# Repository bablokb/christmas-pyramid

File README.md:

A 3D-printed, Motor-driven Christmas Pyramid
============================================

Introduction
------------

This project is about building a christmas pyramid with a motor driven
turntable, lightning and music (click on the image above to see it in
action). There are three distinct parts: the electronics, the software
and the 3D-design. A fourth part, a selfmade pcb is also available,
but not necessary. I only use it because it minimizes cables.

The electronics uses cheap parts that are widely available. The software is
implemented in CircuitPython and mostly portable. The 3D build uses
easy to print parts that can be assembled without glue.

Besides the "big" version with multiple levels, a simplified version is
also available:

This version only has three printed parts: the base, the wall and the
plate. It uses a neopixel-ring instead of LEDs, otherwise
it uses the same electronics as the normal version of the pyramid.

Details
-------

Read about

  - [Electronics](./doc/electronics.md)
  - [Software](./doc/software.md)
  - [3D-Printing](./doc/printing.md)
  - [Support-PCB](./doc/pcb.md)

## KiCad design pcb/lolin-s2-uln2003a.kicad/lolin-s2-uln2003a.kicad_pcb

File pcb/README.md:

KiCAD Source Files for the Support PCB
======================================

For details, read [pcb.md](../doc/pcb.md).

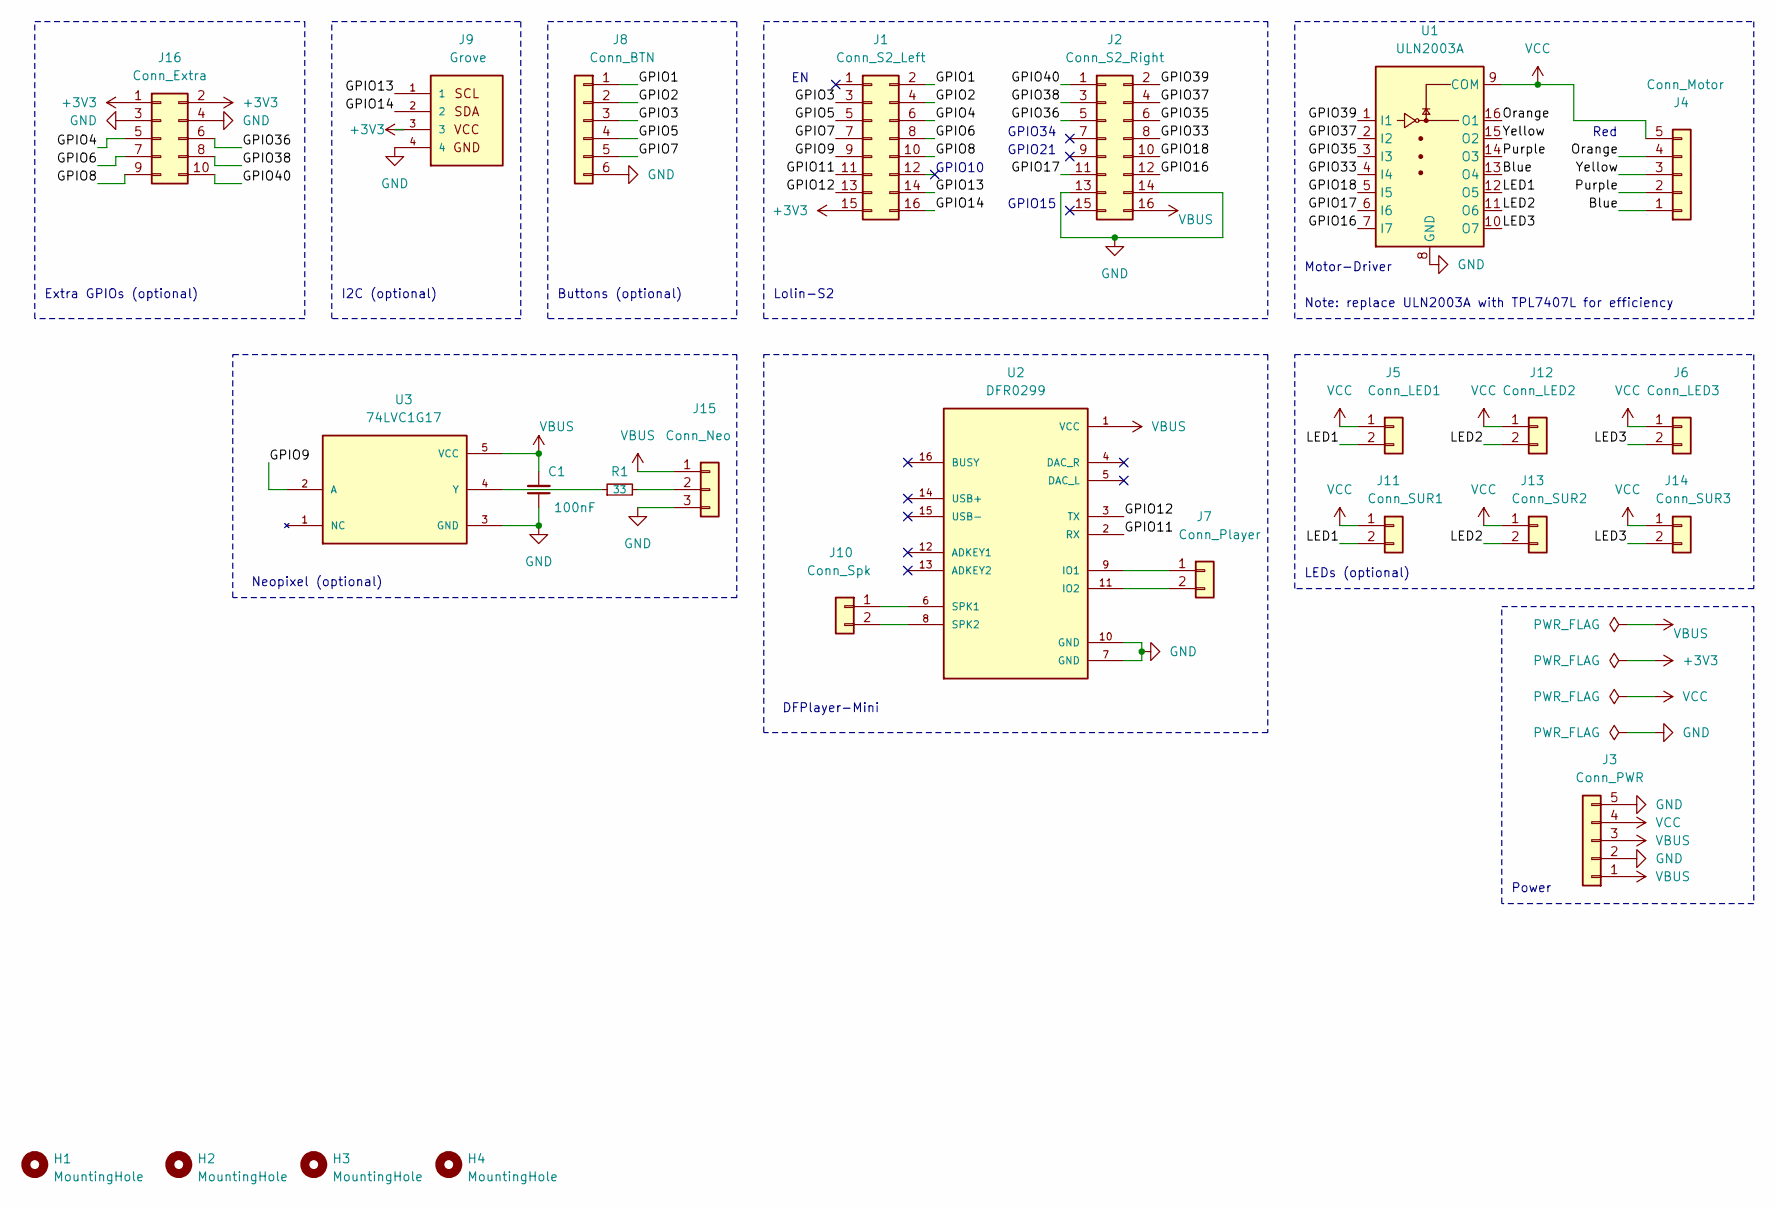
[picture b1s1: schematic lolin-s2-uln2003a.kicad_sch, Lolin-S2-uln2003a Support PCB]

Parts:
C1: 100nF; C_0402_1005Metric; LCSC C1525
H1, H2, H3, H4: MountingHole; MountingHole_2.5mm
J1: Conn_S2_Left; PinSocket_2x08_P2.54mm_Vertical
J2: Conn_S2_Right; PinSocket_2x08_P2.54mm_Vertical
J3: Conn_PWR; PinHeader_1x05_P2.54mm_Vertical
J4: Conn_Motor; JST_XH_B5B-XH-A_1x05_P2.50mm_Vertical
J5: Conn_LED1; JST_XH_B2B-XH-A_1x02_P2.50mm_Vertical
J6: Conn_LED3; JST_XH_B2B-XH-A_1x02_P2.50mm_Vertical
J7: Conn_Player; JST_XH_B2B-XH-A_1x02_P2.50mm_Vertical
J8: Conn_BTN; PinHeader_1x06_P2.54mm_Vertical
J9: Grove; grove_horizontal
J10: Conn_Spk; JST_XH_B2B-XH-A_1x02_P2.50mm_Vertical
J11: Conn_SUR1; JST_SUR_BM02B-SURS-TF_1x02-1MP_P0.80mm_Vertical; LCSC C385130
J12: Conn_LED2; JST_XH_B2B-XH-A_1x02_P2.50mm_Vertical
J13: Conn_SUR2; JST_SUR_BM02B-SURS-TF_1x02-1MP_P0.80mm_Vertical; LCSC C385130
J14: Conn_SUR3; JST_SUR_BM02B-SURS-TF_1x02-1MP_P0.80mm_Vertical; LCSC C385130
J15: Conn_Neo; JST_XH_B3B-XH-A_1x03_P2.50mm_Vertical
J16: Conn_Extra; PinHeader_2x05_P2.54mm_Vertical
R1: 33; R_0402_1005Metric; LCSC C25105
U1: ULN2003A; SOP-16_3.9x9.9mm_P1.27mm; LCSC C7512
U2: DFR0299
U3: 74LVC1G17; 74LVC1G17GW_125; LCSC C426705

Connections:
+3V3: J1.15, J9.3, J16.1, J16.2
/Blue: J4.1, U1.13 (O4)
/GPIO1: J1.2, J8.1
/GPIO2: J1.4, J8.2
/GPIO3: J1.3, J8.3
/GPIO4: J1.6, J16.5
/GPIO5: J1.5, J8.4
/GPIO6: J1.8, J16.7
/GPIO7: J1.7, J8.5
/GPIO8: J1.10, J16.9
/GPIO9: J1.9, U3.2 (A)
/GPIO11: J1.11, U2.2 (RX)
/GPIO12: J1.13, U2.3 (TX)
/GPIO13: J1.14, J9.1
/GPIO14: J1.16, J9.2
/GPIO16: J2.12, U1.7 (I7)
/GPIO17: J2.11, U1.6 (I6)
/GPIO18: J2.10, U1.5 (I5)
/GPIO33: J2.8, U1.4 (I4)
/GPIO35: J2.6, U1.3 (I3)
/GPIO36: J2.5, J16.6
/GPIO37: J2.4, U1.2 (I2)
/GPIO38: J2.3, J16.8
/GPIO39: J2.2, U1.1 (I1)
/GPIO40: J2.1, J16.10
/LED1: J5.2, J11.2, U1.12 (O5)
/LED2: J12.2, J13.2, U1.11 (O6)
/LED3: J6.2, J14.2, U1.10 (O7)
/Orange: J4.4, U1.16 (O1)
/Purple: J4.2, U1.14 (O3)
/Yellow: J4.3, U1.15 (O2)
GND: C1.1, J2.13, J2.14, J3.2, J3.5, J8.6, J9.4, J15.3, J16.3, J16.4, U1.8 (GND), U2.7 (GND), U2.10 (GND), U3.3 (GND)
unnamed: J7.1, U2.9 (IO1)
unnamed: J7.2, U2.11 (IO2)
unnamed: J10.1, U2.6 (SPK1)
unnamed: J10.2, U2.8 (SPK2)
unnamed: J15.2, R1.2
unnamed: R1.1, U3.4 (Y)
VBUS: C1.2, J2.16, J3.1, J3.3, J15.1, U2.1 (VCC), U3.5 (VCC)
VCC: J3.4, J4.5, J5.1, J6.1, J11.1, J12.1, J13.1, J14.1, U1.9 (COM)

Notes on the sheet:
Lolin-S2
Buttons (optional)
Note: replace ULN2003A with TPL7407L for efficiency
Motor-Driver
Neopixel (optional)
GPIO21
GPIO34
GPIO10
Red
Power
Extra GPIOs (optional)
GPIO15
DFPlayer-Mini
LEDs (optional)
I2C (optional)

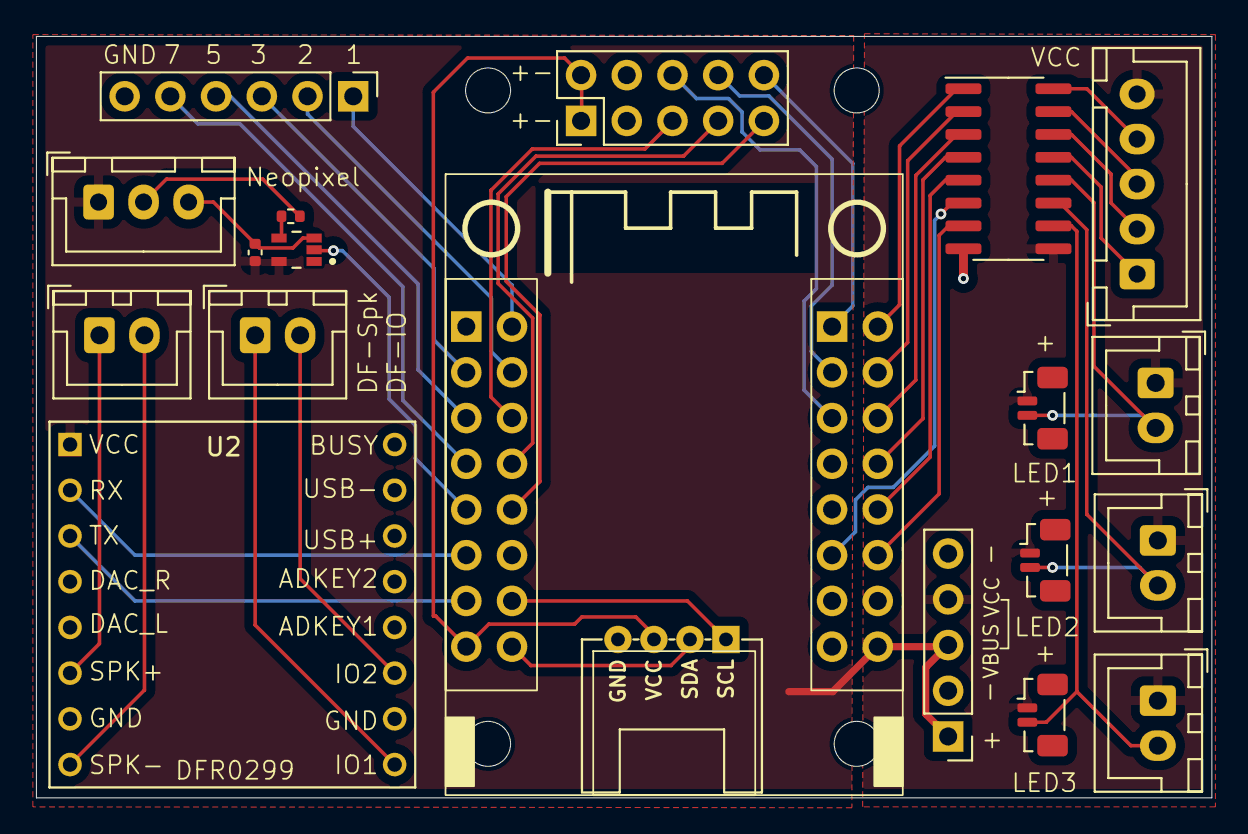
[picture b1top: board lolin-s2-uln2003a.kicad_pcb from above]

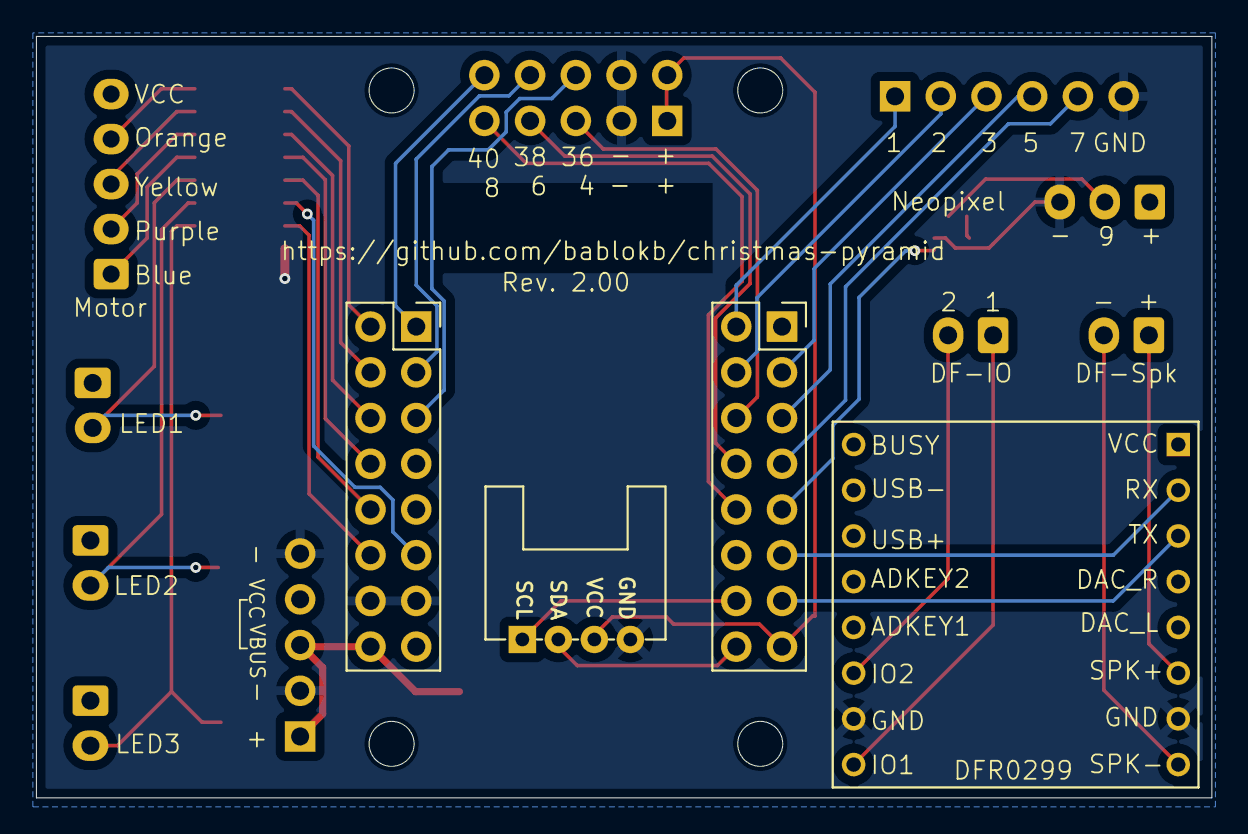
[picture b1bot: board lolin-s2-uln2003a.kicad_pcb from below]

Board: 2 copper layers, 65.3 x 42.3 mm, 25 parts (2 on the bottom side), 40 nets.

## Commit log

2025-06-16 Rev. 1.00 files for motor-pcb
2025-06-16 created .gitignore
2025-06-16 added wip notice
2025-06-17 first draft base of pyramid
2025-06-17 change inner diameter of motor-support
2025-06-17 set base-size to 85
2025-06-17 fix position of pcb-holder
2025-06-20 initial version pcb-holder
2025-06-20 add cutout for SD-card
2025-06-20 use parameters for wall-cutout
2025-06-20 add wall-cutout, fix pcb-holder orientation
2025-06-20 post(): use cyl for preview and star for final rendering
2025-06-20 fine-tune cutouts, cone and total height
2025-06-24 added cutout for LED-cable from base to first level
2025-06-27 add models for base-level walls
2025-06-27 model for LED-strips (for background lighting)
2025-06-28 wall_pcb(): add cutouts for air-flow
2025-06-28 add cutout for air-flow
2025-06-28 tilt cutout for LED-cable
2025-07-02 enlarge USB-C cutout
2025-07-07 add cutout for motor-cable
2025-07-07 fix: post(): add cone alignment to BOTTOM+CENTER
2025-07-07 add 'level_scale'
2025-07-07 initial design level1
2025-07-10 add cutouts to outer posts and cutouts to floor
2025-07-10 add dimensions for level1
2025-07-10 first iteration fences for level1
2025-07-11 fence-posts: only cutout upper third to increase stability
2025-07-11 add cutout height for fence-posts
2025-07-11 add cutouts for fences because cutout of posts are no longer full height
2025-07-14 implement button-holder
2025-07-14 add button-holder to wall_pcb()
2025-07-14 fine tune inner cutout fence-post
2025-07-16 fine-tune cutout for USB-C
2025-07-16 add some more cutout-depth for fences (simplify 3D-printing)
2025-07-16 added cable-holders
2025-07-18 fence-post: fine-tune cutout for base-cone
2025-07-18 add chamfer
2025-07-19 reordered base-plate objects; added module lamp_shade()
2025-07-19 fine tune fence-post cutout again
2025-07-21 initial commit of source-code
2025-07-21 exclude 'lib'
2025-07-21 refactored turntable-plate to tt_plate.scad
2025-07-21 change from 6 to 4 level1-posts
2025-07-21 refactor dimensions from tt_plate.scad to shared.scad
2025-07-21 wait at most config.WAIT4CONSOLE seconds for console
2025-07-22 move level1-posts to the center
2025-07-22 cutouts for level1-posts only in the upper third
2025-07-22 removed some trailing white-space
2025-07-22 use different effect
2025-07-22 fix next/prev file-switching
2025-07-23 added nativity-fence; fine-tune all fences
2025-07-24 add dimensions for level1 walls
2025-07-24 replace hard-coded values with values from shared.scad
2025-07-24 designed walls for level1
2025-07-30 add level2 dimensions
2025-07-30 initial implementation of level2
2025-08-02 callbacks: add debug-messages
2025-08-02 fix: expose inc_rpm() instead of set_rpm()
2025-08-02 fix: don't switch to next song when current song was interrupted
2025-08-08 reduce level2 fence height
2025-08-08 add cutout for cable
2025-08-14 add cutouts for all posts
2025-08-14 add cutouts for central plate, hole and cable
2025-08-14 add a central plate
2025-08-19 added PINS_SD
2025-08-25 switch to different gear-ratio; turn debugging off
2025-08-25 fixed gain-labels on F.Silkscreen
2025-08-25 fixed rotation of motor-connector
2025-08-25 symmetric mounting holes
2025-08-25 update after fixing unsymmetric mounting holes
2025-08-25 remove label J9
2025-08-25 update images
2025-08-25 update due to production-file generation
2025-08-25 updated gerber-files for Revision 1.01
2025-08-27 add pins for DFPlayer (UART)
2025-08-27 switch to new player implementation
2025-08-27 minor change in message-text
2025-08-27 switch implementation from I2S to DFPlayer
2025-08-29 Rev. 2.00 of support-pcb
2025-09-09 pcb_holder: updated screw-offsets for Rev 2.00 board
2025-09-09 larger offset for cable-holders
2025-09-11 simplify lamp_shade()
2025-09-11 adapt for Rev 2.00 PCB
2025-09-15 add src/lib to repository
2025-09-15 provide library-files as part of the repo
2025-09-17 flip orientation of button-holder
2025-09-17 improve pcb-wall
2025-09-17 added documentation
2025-09-17 added model-files for silhouettes/cutouts
2025-09-17 added note about production-files
2025-09-18 pcb_holder(): refactor special supports to pcb_holder_special() (and use this in base.scad)
2025-09-20 be more specific about necessary mcu-pins
2025-09-20 initial content
2025-09-20 added/fixed links to images
2025-09-20 added images
2025-09-20 fixed spelling of filename
2025-09-20 fix markup
2025-09-22 support subset of buttons/callbacks
2025-09-22 activate second and third channel
2025-09-22 also pass callback-numbers to Buttons-constructor
2025-09-22 fix: pause(): toggle self._playing
2025-09-22 added image of Lego-Lighting wires
2025-09-25 run(): add explicit play() after random()
2025-09-25 design change: higher, with cutouts for spots
2025-09-26 fixed size of cutouts for spots
2025-09-26 refactoring: move code for cable-channels to module c_channels()
2025-09-26 redesign: move cable-channels to level2
2025-09-26 increased size of level2-posts/level2-fence
2025-09-26 fix: layer-height for level2-fence/figures
2025-09-27 initial version simple base
2025-09-27 added USB-C cutout
2025-09-27 refactored motor-dimensions to motor_dims.scad
2025-09-27 doubled height of motor-posts
2025-09-27 code cleanup (dimensions)
2025-09-27 added holder for speaker
2025-09-29 refactoring: move shared dimensions to simple_shared.scad
2025-09-29 initial design simple wall
2025-09-29 symmetric design
2025-09-29 fine-tune dimensions
2025-09-29 redesign (more FDM-friendly)
2025-09-30 optimize height, add comments
2025-09-30 change top-most ring to a inverted cone
2025-09-30 add more strength to motor-posts
2025-10-03 refactored top-diameter to simple_shared.scad
2025-10-03 refactoring: make tt_plate a reusable module
2025-10-04 fix: add .forever() to candle()
2025-10-06 support optional tasks
2025-10-06 add configuration for simple-build
2025-10-06 switch to own implementation of animation
2025-10-06 added adafruit_pixelbuf and neopixel libraries
2025-10-08 support a variable number of buttons
2025-10-08 pass number of buttons to button_holder()
2025-10-09 introduce h_btn_holder
2025-10-09 initial design for turn-table plate for simple-base
2025-10-09 integrated button-holder
2025-10-09 introduce h_add parameter
2025-10-09 print with or without button-holder
2025-10-13 updated and added images
2025-10-15 updated test-examples
2025-10-15 support recessed buttons
2025-10-15 revert simple_wall to version without button-holder
2025-10-15 DFPlayer: shrink cutout+lid of second cutout
2025-10-15 DFPlayer: shrink first cutout to match second cutout
2025-10-15 add button-holder
2025-10-15 revert simple_base.scad (no button-holder, large DFPlayer cutout)
2025-10-15 re-add button-holder
2025-10-21 change width of 2-btn holder
2025-10-23 set initial volume to 80
2025-10-23 use config_pcb for configuration
2025-10-23 added link to AliExpress
2025-10-23 add links to amphora and treasure-chest
2025-10-23 create all walls together
2025-10-23 print all shades at once
2025-10-23 add info about simplified version
2025-10-23 add notes about LEDs on motor-driver board and about DFPlayer versions
2025-10-23 update list of precompiled libs
2025-10-24 print all walls at once
2025-10-24 optimize star-cutouts
2025-10-24 print all fences at once
2025-10-24 add mapping scad->stl
2025-10-24 added STL-models
2025-10-25 updated to final version
2025-10-25 add video
2025-10-25 link to video
2025-10-25 add info about clickable image
2025-10-25 added stop message
2025-10-25 on stop, turn leds off and deinit
2025-10-25 reimplement processing of KeyboardInterrupt/Exception
2025-11-01 speed-up COLOR_CHANGE (5->1)
2025-11-01 updated configuration
2025-11-22 add image of the simple version and update Readme
